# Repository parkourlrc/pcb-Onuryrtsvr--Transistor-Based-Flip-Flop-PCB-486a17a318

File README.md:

# Transistor Based Flip-Flop Circuit

### Hardware Specifications
- **PCB Type:** Single Sided (Bottom Layer)
- **Minimum Track Width:** 0.4 mm
- **Minimum Clearance:** 0.5 mm
- **Board Dimensions:** 51 mm x 28 mm

## 📂Files
- **/kiCad-Project**: KiCad project files (.kicad_pcb, .kicad_sch).
- **/Fabrication**: Gerber and Drill files. Mirrored pdf file of the PCB.
- **/Images**: schematic, PCB images.

## 📋Footprints:
**Capacitors:** Capacitor_THT:CP_Radial_D5.0mm_P2.00mm
**Leds:** LED_THT:LED_D5.0mm
**Connector:** Connector_PinHeader_2.54mm:PinHeader_1x02_P2.54mm_Vertical
**Resistor:** Resistor_THT:R_Axial_DIN0207_L6.3mm_D2.5mm_P7.62mm_Horizontal
**Transistor:** Package_TO_SOT_THT:TO-92_Inline
**Switch:** Button_Switch_THT:SW_Slide-03_Wuerth-WS-SLTV_10x2.5x6.4_P2.54mm

**Design:** Onur Yurtsever

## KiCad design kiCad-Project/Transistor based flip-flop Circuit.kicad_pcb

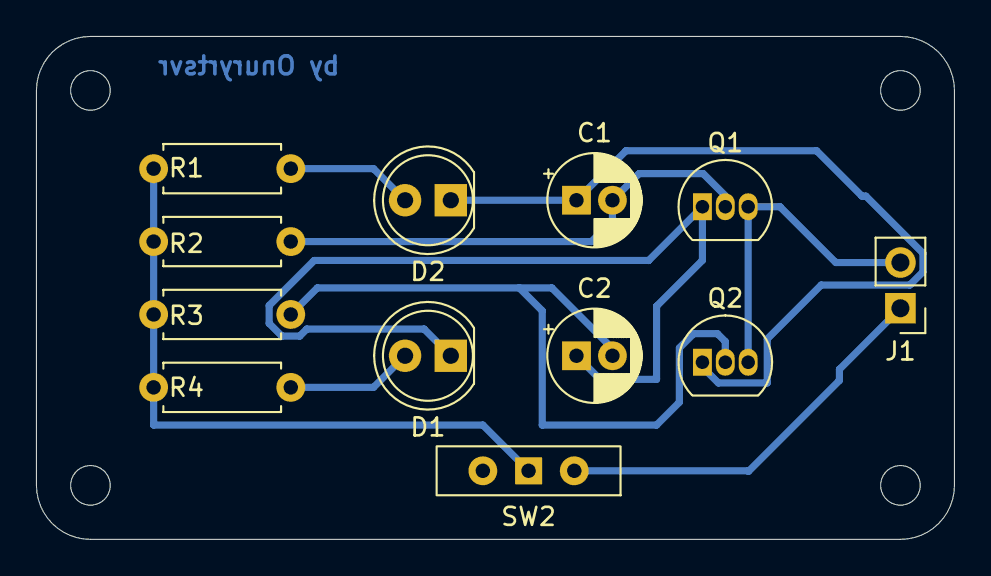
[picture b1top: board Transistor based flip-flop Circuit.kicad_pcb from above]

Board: 2 copper layers, 51.0 x 27.9 mm, 12 parts (0 on the bottom side), 9 nets.

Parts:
C1, C2: 80u; CP_Radial_D5.0mm_P2.00mm
D1, D2: LED; LED_D5.0mm
J1: Conn_01x02; PinHeader_1x02_P2.54mm_Vertical
Q1, Q2: BC547; TO-92_Inline
R1, R4: 470; R_Axial_DIN0207_L6.3mm_D2.5mm_P7.62mm_Horizontal
R2, R3: 10K; R_Axial_DIN0207_L6.3mm_D2.5mm_P7.62mm_Horizontal
SW2: SW_SPDT; SW_Slide-03_Wuerth-WS-SLTV_10x2.5x6.4_P2.54mm

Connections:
/BAT+: J1.1, SW2.2 (B)
/BAT-: Q1.3 (E), Q2.3 (E)
unnamed: D1.2 (A), R4.1
unnamed: C2.1, D1.1 (K), Q1.1 (C)
unnamed: D2.2 (A), R1.1
unnamed: C1.1, D2.1 (K), Q2.1 (C)
unnamed: C1.2, Q1.2 (B), R2.1
unnamed: C2.2, Q2.2 (B), R3.1
unnamed: R1.2, R2.2, R3.2, R4.2, SW2.1 (A)

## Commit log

2026-04-04 README.md
